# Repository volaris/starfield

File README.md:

Starfield
=========

Software (simulation and control) and electronics for the starfield display.

## Overview

The Starfield is a large grid of color controllable LEDs. They're spaced on vertical strands so that people can walk through them. People will be able to watch it from afar, walk through, or lounge in the space. There will be ambient animations designed to calm and intrigue. Calming music will play throughout the space. At certain times a DJ can connect to the Starfield or it picks up noise in the environment and displays animations that enhance and respond to that sound. IR cameras will detect where people are in the space and how active they are and modify the animations to respond to them. In the future, hand tracking stations will be used to create an individual or collaborative animation looper. Other methods of interaction such as converting EEG patterns to light are being investigated. The first version is a prototype designed to fit in a living room. A 20'x20'x20' version is being constructed for [Critical NW 2015](http://www.criticalnw.org/) and an even larger one is being planned for Burning Man 2016.

## Get Involved

Read the developer's guide and documentation at [volaris.github.io/starfield](http://volaris.github.io/starfield/)

## Technical Details

The core of the Starfield is driven by a [Fadecandy](https://github.com/scanlime/fadecandy) running on a [Raspberry Pi](https://www.raspberrypi.org/).

### Prototype

The prototype Starfield is a 7x5x4 voxel grid designed for hardware, animation, and construction technique testing.

### Critical NW

The Critical NW Starfield is a 11x11x10 voxel grid.

### Burning Man

The Burning Man Starfield is a 16x16x15 voxel grid.

## Repository Layout
```
/starfield
    /controllers - Starfield drivers and control software
        /AlgorithmDemo - Single display algorithm wrapper, displays list of all available drivers and their configuration options
        /Ambient - Randomly cycles through ambient algorithms
        /DualController - like AlgorithmDemo except it splits the display and displays two different algorithms
        /StarfieldDrivers - all of the driver classes, the controllers listed above use reflection to enumerate the drivers and their types from this library
    /docs - Starfield documentation for generating [volaris.github.io/starfield](http://volaris.github.io/starfield/)
    /documentation - Papers, datasheets, images related to algorithms 
    /electronics - Electronics designs: power distribution, voxel design, etc.
    /lib - Shared code and utility classes
        /.NET - .NET utility classes
            /StarfieldClient - base starfield classes, types, and interfaces (includes display model, driver interface, and network protocols)
            /Utils - Math, color, sound, and other algorithm utilities
        /external - 3rd party libraries
    /mechanical - Mechanical engineering designs and calculations for the structure
    /simulator - Unity simulator
```

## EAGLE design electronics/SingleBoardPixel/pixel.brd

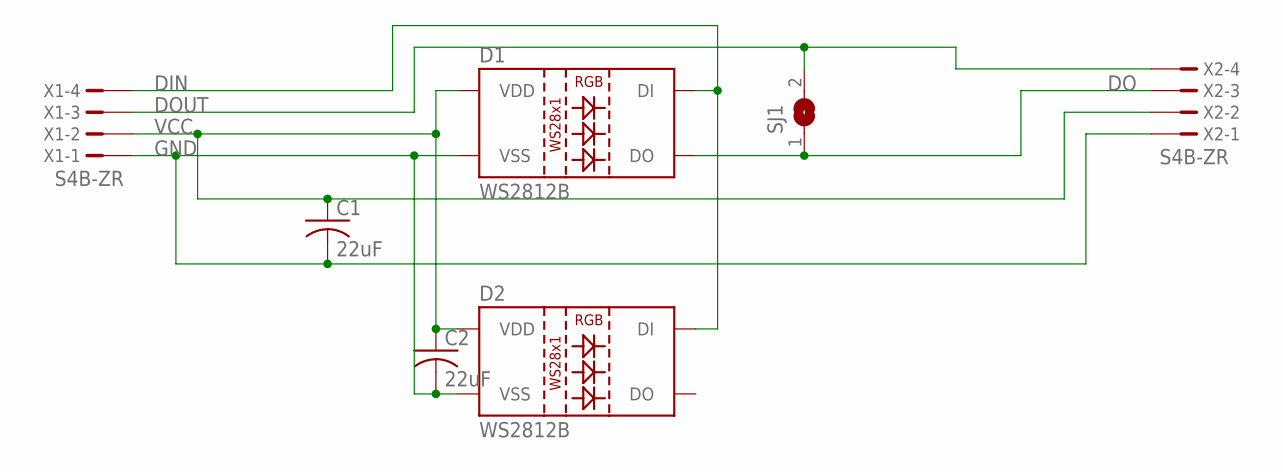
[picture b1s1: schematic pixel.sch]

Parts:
C1, C2: 22uF; C0402
D1, D2: WS2812B
SJ1: SJ
X1, X2: S4B-ZR

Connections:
DIN: D1.4 (DI), D2.4 (DI), X1.4
DO: D1.2 (DO), SJ1.1, X2.3
DOUT: SJ1.2, X1.3, X2.4
GND: C1.2, C2.2, D1.3 (VSS), D2.3 (VSS), X1.1, X2.1
VCC: C1.1, C2.1, D1.1 (VDD), D2.1 (VDD), X1.2, X2.2

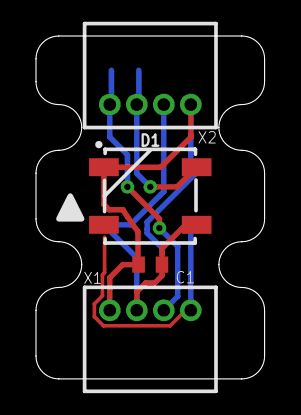
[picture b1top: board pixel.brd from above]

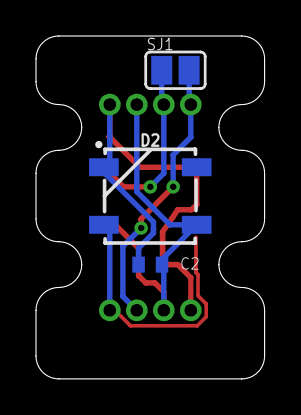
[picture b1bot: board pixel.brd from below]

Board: 2 copper layers, 12.7 x 19.1 mm, 7 parts (3 on the bottom side), 5 nets.

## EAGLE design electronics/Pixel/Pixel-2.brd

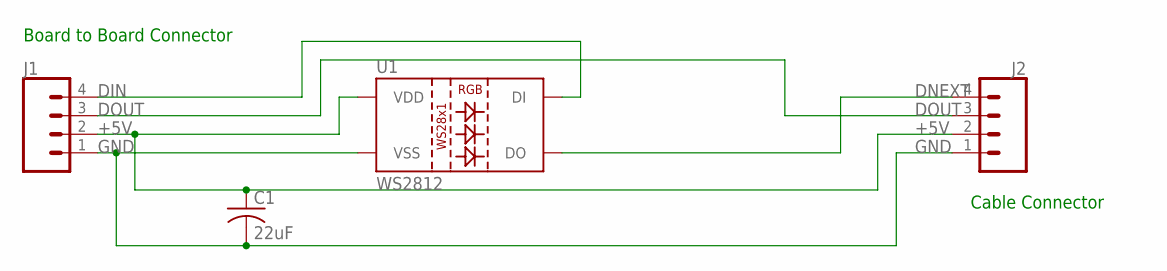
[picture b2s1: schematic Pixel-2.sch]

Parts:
C1: 22uF; C0402
J1, J2: CONN_04; 1X04
U1: WS2812; LED-TRICOLOR-5050-IC

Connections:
+5V: C1.1, J1.2, J2.2, U1.3 (VDD), U1.5 (VDD)
DIN: J1.4, U1.2 (DI)
DNEXT: J2.4, U1.1 (DO)
DOUT: J1.3, J2.3
GND: C1.2, J1.1, J2.1, U1.6 (VSS)

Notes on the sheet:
Cable Connector
Board to Board Connector

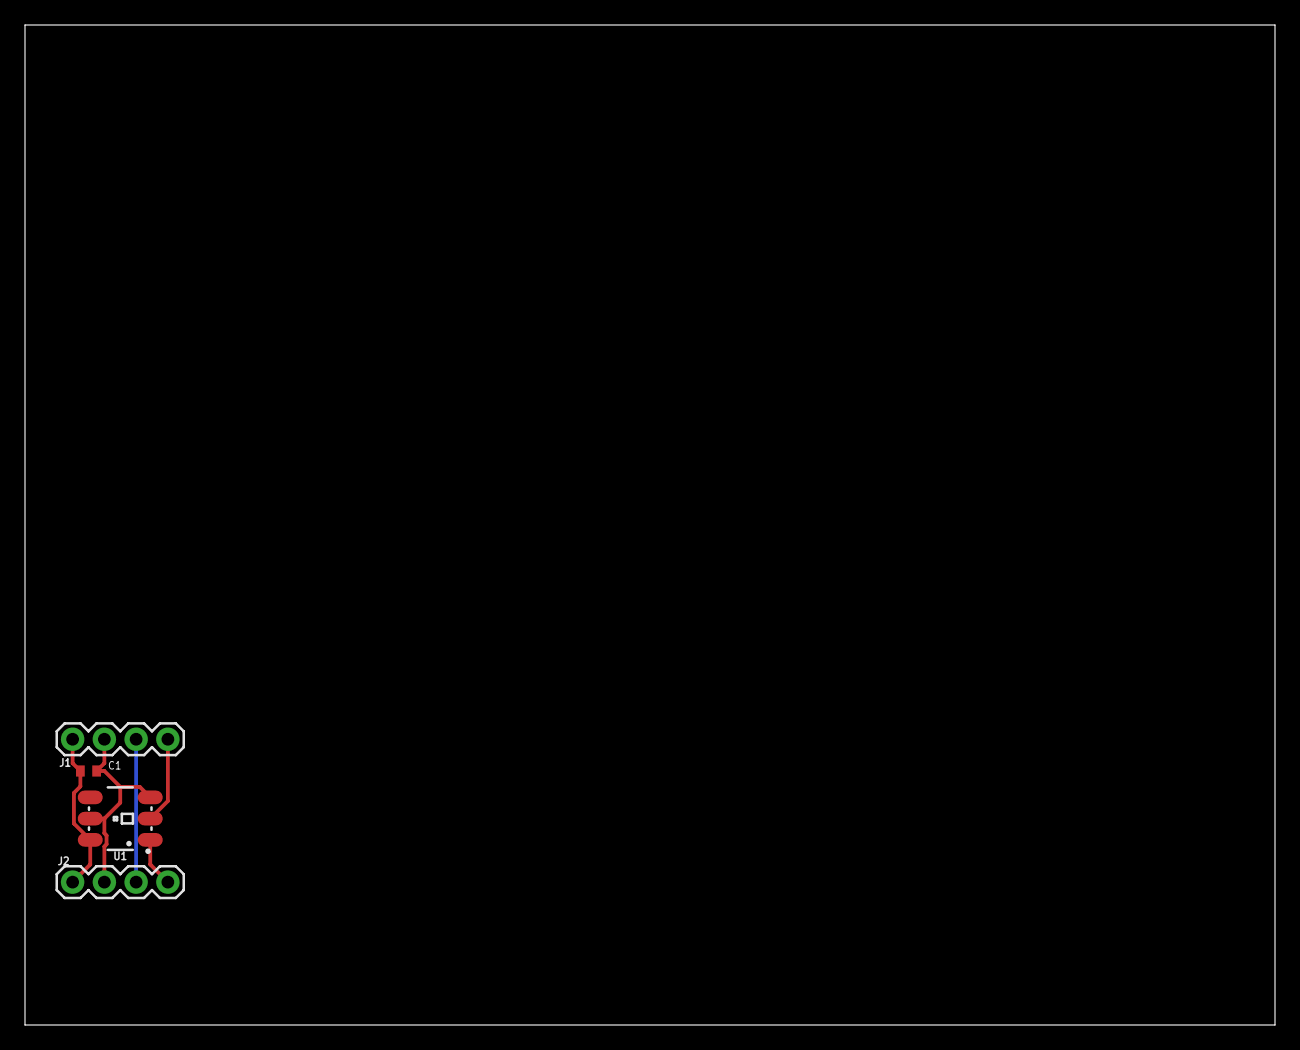
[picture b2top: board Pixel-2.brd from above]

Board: 2 copper layers, 100.0 x 80.0 mm, 4 parts (0 on the bottom side), 5 nets.

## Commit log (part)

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2015-02-28 Adding .gitignore
2015-02-28 Initial commit of software and electronics
    Software: Various demo algorithms and the .NET library for controlling
    the starfield.
    Electronics: The pixel power and data distribution boards
2015-02-28 Louie's Mechanical Drawings
    Overview drawings and Caternary equations for the Starfield.
2015-02-28 Updating .gitignore for Unity
2015-02-28 Simulator
    Adding the Unity based simulator.
2015-03-04 Cleanup, UI Improvements, and Driver Improvements
    Cleanup:
    Started effort to standardize naming conventions, add code folds, and
    wrap members with properties.
    UI Improvements:
    Added dropdown to select starfield type, IP address and port fields, and
    a property grid to allow driver configuration on the fly.
2015-03-04 Continued Code Cleanup
2015-03-07 Refactoring Common Utilities into Separate lib
    Moving the shared utility classes to their own library. Removing
    dependency on Leap Motion classes for math.
2015-03-08 Completed Refactoring
    All algorithms are now in a separate DLL to be used by the debug
    algorithm demo app and the Starfield control server.
2015-03-08 Cleanup Unused Script
2015-03-08 More cleanup
2015-03-09 Updating .gitignore
    *.meta files are needed for the unity simulator. C# projects in VS don't
    generate files with this extension so this should not result in
    commiting extra files.
2015-03-09 New Static IP
2015-03-09 Fixing Incorrect Axes
2015-03-09 Implemented Regeneration in the Simulator
    Now the user can dynamically change the size of the Starfield in the
    simulator.
2015-03-09 Updating Simplex Driver Defaults
2015-03-13 StarfieldClient Updates
    Refactored field names and added brightness control.
2015-03-14 Updating .gitignore and checking in missed files
2015-03-14 adding test code
2015-03-15 breaking out .gitignore
2015-03-15 Game of Life Driver
    This doesn't compute in the render window, so will need to have its
    processing broken out into a thread.
2015-03-15 More Cleanup
    Adding comments to the platform classes.
2015-04-01 Render Pausing Support
    Adding support to pause the rendering.
    Fixed a bug where the StarfieldClient was not initialized before the
    initial algorithm was started.
    Set the defaults target to be the Critical Starfield on localhost.
2015-04-01 Game of Life
    Finishing the basic implementation of the game of life. Thresholds and
    initial generation still needs to be tweaked.
2015-04-09 Comment and Bug Fixes
    Additional comments, a comment fix, and a fix for a bug in the vector
    math.
2015-04-10 Fading Static Bug Fix
    For some colors, when a voxel faded to 0, it would flash brightly before
    staying at 0. This has been prevented and added as a driver option.
2015-04-10 Form Demo Shrinking Starfield is Broken
    When selecting a smaller Starfield size, an exception is thrown.
2015-04-10 ColorUtils.GetColorGradient Fix
    The bounding in the GetColorGradient doesn't work in all cases.
    Switching to simpler, more correct math.
2015-04-13 README layout fix
2015-04-13 README layout take 3
2015-04-13 README updates
2015-04-13 README fix
2015-04-13 README layout
2015-04-15 Docs Reorganization
2015-04-15 Fixing Build Warnings
2015-04-22 Initial Mixer and Color Space Conversion Checkin
2015-04-22 Updating Mixer Class
2015-04-22 Reference Changes
    These changes should allow easier usage when changing between VS and
    Xamarin and different computers. Also checking in a few animations.
2015-04-22 Color Space Support
    Adding support in the utils library for various color spaces and color
    space conversions. This is a work in progress.
2015-04-22 Initial Mixer Checkin
    Adding the mixer class. This is a work in progress.
2015-04-22 Color Space Support
    Finishing the color space conversion class.
2015-04-22 Adding TCPStarfieldServer
2015-04-22 Project Refactoring
    Making it easier to build everything using fewer projects. Now each
    control program will build the drivers library and there is a single
    solution for all of the libs.
2015-04-22 Project Refactoring
    Submitting a file I missed in the checkin.
2015-04-22 DriverType Support
    Adding support for runtime identification of driver types.
2015-04-24 Tagging Driver Types
2015-04-26 Ambient Controller
    This controller will randomly walk through the algorithms tagged as
    ambient and transition smoothly between them. Great for not having to
    manually switch algorithms, not so great for showing off specific ones
    or customize them.
2015-08-13 Dual Controller and Ambient Controller
2016-02-17 New Noise Algorithms
    Testing out some new noise based algorithms, including some that are
    sound responsive.
2016-02-18 Sound Responsive Simplex Clouds
    Cloud display threshold is determined by EQ level.
2016-02-27 New Smoke Variant
    This one is sound responsive and changes colors with the artifacts.
2016-02-27 Adding First Version Binaries
2016-02-27 2nd Version Binaries
2016-02-27 Current Build
2016-03-03 updated readme
    more detail for repo layout
2016-03-03 Sound Processor Refactoring and NullSoundProcessor
    refactoring missed in the last checkin and the null sound processor for
    OSX and *nix
2016-03-03 Documentation
    Starting documentation for the simulator.
2016-03-05 Create snakes.cs
    mildly sound responsive snakes that traverse the starfield
2016-03-05 added snakes algorithm
2016-03-26 Adding image blender
    This program blends up to 5 cameras into a single image. This composite
    image represents the heat map that will feed the presence and activity
    responsive display algorithms.
2016-03-26 Fixing camera 5 draw location
2016-03-26 Documentation
    Some basic docs
2016-03-27 Adding image_processor.py
    This script analyzes the blended image and creates an activity index for
    each pixel.
2016-03-29 Adding verbose output for debug view
2016-03-30 Changing Activity JSON Format
2016-03-30 Adding Top Level Script
2016-03-30 Adding vision system demo viewer
2016-03-30 updating .gitignore for top down vision system
2016-03-30 adding windows support
2016-04-01 Vision System is Working!
    Just waiting on the hardware from mcmaster to test it in a scale model.
2016-04-01 removing ssh key stuff, since we're using http now
2016-04-04 Vision System Improvements and Tooling
    * Performance improvements for the vision system.
    * Presence simulator
    * Sample presence responsive algorithm
2016-04-04 Various Algorithms
    Not all of them are finished, but everything builds.
2016-04-06 More algorithms to react to presence
2016-04-06 Updating controller binaries
2016-04-06 fixing bug when starfield size is cahnges
2016-04-06 fixing driver type
2016-04-06 adding presence trails driver
2016-04-16 New Algorithms
    Finished some algorithms I started a while back and added a few more.
2016-04-17 more algorithms!
2016-05-21 various fadecandy configs
2016-05-21 additional external libs
2016-05-21 updated vision system config
2016-05-21 updating vision system
2016-05-21 updating vision system
    missed a file
2016-05-28 Presence Worker Thread
    Moving the timer to a worker thread to help with connectivity timeouts.
    If the server wasn't running, many instances of the client thread would
    be created starving the render thread of resources. This way, there is
    only ever one thread to do the polling.
2016-05-28 First Presence Game
    This is a simple whack a mole style game. A target is displayed and as
    soon as people move to it, the target moves.
2016-05-29 whackamole improvements
2016-05-30 Onset Detection
    It isn't perfect, but it works better than the naive artifact detection.
    Needs to be tweaked for beat detection.
2016-05-30 Onsets Per Minute Calculation
2016-08-17 Adding support for KekeMohy
2016-08-17 Modifying references to have relative paths
2016-08-17 Adding Raver Plaid
2016-09-22 kekemohy config fix
2016-09-22 reference fix
2016-09-22 test fill restart fix
2016-09-22 safety fix
2016-09-22 New drivers
2016-09-24 Driver List Generator
    Tool that generates lists of controllers with custom settings
2016-09-24 3d vector math
2016-09-25 JSON configurable controller
2016-09-30 consolidating driver loading
2017-01-04 missed file in earlier commit
2017-02-08 Documentation Generation
2017-02-08 clipper lib for advanced geometric operations
2017-02-16 Models for Resin Work
2017-02-17 Documentation and Refactoring
2017-02-17 Smooth Molds for Resin Work
2017-02-17 link to more robust distance
2017-02-17 added todo
2017-02-17 API docs
2017-02-17 Set theme jekyll-theme-slate
2017-02-21 Documenation Images
2017-02-21 readme update
2017-02-22 more documentation
2017-02-25 Enabling Python Drivers
    Added an IronPython binding so that drivers can be written in python in
    addition to C#.
2017-02-25 Documentation Fix
2017-02-28 Set dependencies to make build solution work
2017-02-28 Starting a new github.io homepage
2017-02-28 Percent Mixer
    This class will enable interesting combinations of starfield animations.
    Incluidng animations with the only purpose of turning on/off or dimming
    certain pixels in combination with a colorful animation.
2017-02-28 Added the mixer to the project
2017-03-14 2D Projection
2017-03-14 Simulator Builds
2017-03-14 Documentation Updates
2017-03-14 2D Projection - Missed Files
2017-03-14 Documentation
2017-03-14 v1 structural models
2017-03-14 simulator files
2017-03-25 new molds
2017-04-28 make debug builds work the same as release
2017-05-05 Set theme jekyll-theme-cayman
2017-05-05 first attempt at jekyll themes
2017-05-05 update base_url
2017-05-05 moving doc files around
2017-05-05 fix namespace link
2017-05-05 added contributing steps
2017-05-19 add simulator doc
2017-05-19 adding instructions for sim'
2017-05-19 add instructions for running algo demo
2017-05-19 added anatomy of an algo
2017-05-19 added how to write a plugin
2017-05-19 Documentation Update
    Updated documentation project to use the right folder. Regenerated
    documentation.
2017-05-19 Arduino Strand Test Rig Code
2017-05-19 cleaned up md formatting
2017-05-22 Deployment Project
    This project just references all the other projects so that all of the
    binaries are collected for deploying to the starfield.
2017-05-24 Adding starfield and utils projects to drivers
2017-05-24 Fixed issue with click-once signing
2017-05-26 Pushing Kinect work
2017-05-26 Adding build results from KinectPresenceMonitor
2017-06-02 Moving OPCClient to Async
    This isn't a perfect change, but it works for the moment.
2017-06-10 New Driver
2017-06-10 next version of mlmp
    still experimenting, doesn't work well
2017-06-10 Laser Cut Acrylic Case for Kinects
2017-06-16 Tweaks to build TheWorld solution
    Changed a bunch of relative paths to use SolutionDir, and changed a
    couple References to ProjectReferences
2017-06-20 adding background image
2017-06-20 adding style tags
2017-06-26 20x20x10 config files
2017-07-01 updated releases
2017-07-01 strand test updates
2017-07-01 model updates
2017-07-01 fixing CNW 2017 releases
2017-07-29 Refactor and Complete Kinect Monitor
    Refactored a few things and set up network updates and logging.
2017-08-06 External Loggers
    Removed the logging from the kinect monitor server. Added scripts to
    manage it separately using SDK applications and fmedia. These apps will
    compress the streams and use a lot less storage space.
2017-08-24 usb mic support

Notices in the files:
parts and their libraries:
SparkFun-Connectors: Licensing: Creative Commons ShareAlike 4.0 International - https://creativecommons.org/licenses/by-sa/4.0
